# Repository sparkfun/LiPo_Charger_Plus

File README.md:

SparkFun LiPo Charger Plus
========================================

[*SparkFun LiPo Charger Plus (PRT-15217)*](https://www.sparkfun.com/products/15217)

The SparkFun LiPo Charger Plus is the souped-up power option in the SparkFun line of single-cell lithium polymer (LiPo) battery chargers. With this iteration, we've changed the input charge connector to USB-C and provided charge rate selection as well as optional thermal protection. Charge, power, and done LEDs clearly indicate the status of your charging process. This board can be used for any of the 2-pin JST connector single cell LiPo batteries we carry. 

With an input voltage between 3.75V-6V, the MCP73833 can charge up to a maximum rate of 1000mAh and provides two forms of thermal protection. An internal sensor maintains maximum charging rate until the die temperature of the IC reaches ~95°C; the charge controller will then reduce the charge rate to prevent overheating. The MCP73833 also has an optional input pin for an NTC (negative-temperature coefficient) thermistor, thus gating the battery against possible damage. 

Repository Contents
-------------------

* **/Hardware** - Eagle design files (.brd, .sch)

Documentation
--------------
* **[SparkFun Fritzing Part](https://github.com/sparkfun/Fritzing_Parts/blob/main/products/15217_sfe_LiPo_Charger_Plus.fzpz)** - Fritzing diagrams for SparkFun products.
* **[Hookup Guide](https://learn.sparkfun.com/tutorials/lipo-charger-plus-hookup-guide)** - Basic hookup guide for the SparkFun LiPo Charger Plus.

License Information
-------------------

This product is _**open source**_!

Please review the LICENSE.md file for license information.

If you have any questions or concerns on licensing, please contact technical support on our [SparkFun forums](https://forum.sparkfun.com/viewforum.php?f=152).

Distributed as-is; no warranty is given.

- Your friends at SparkFun.

_<COLLABORATION CREDIT>_

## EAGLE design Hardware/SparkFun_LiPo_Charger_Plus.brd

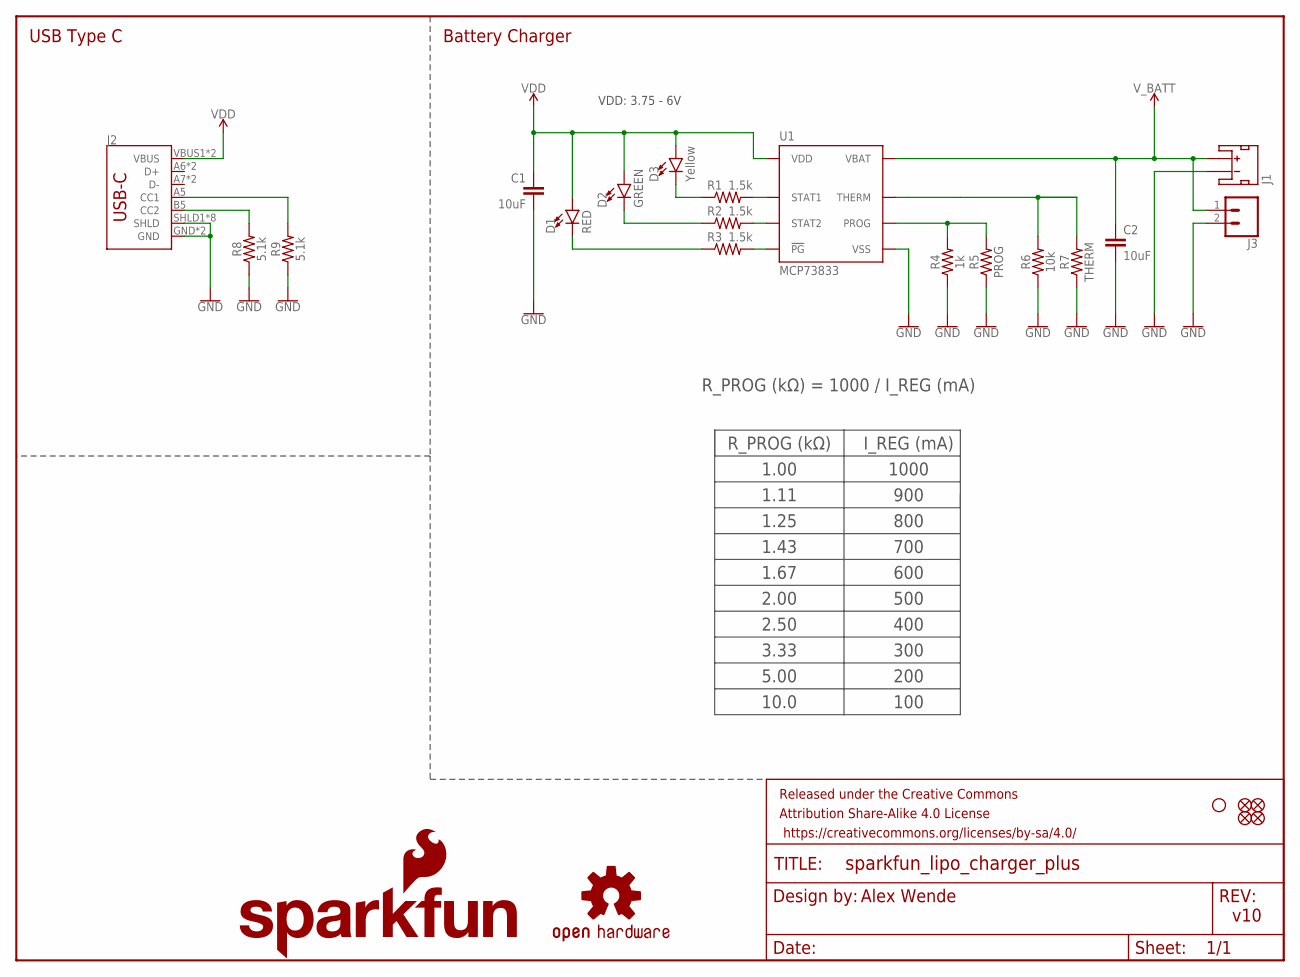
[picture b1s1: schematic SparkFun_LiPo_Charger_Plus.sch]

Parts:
C1, C2: 10uF; 0603
D1: RED; LED-0603
D2: GREEN; LED-0603
D3: Yellow; LED-0603
FD1, FD2, FD3, FD4: FIDUCIALUFIDUCIAL; FIDUCIAL-MICRO
FRAME1: FRAME-LETTER; CREATIVE_COMMONS
H1: STAND-OFF
J1: JST_2MM_MALE; JST-2-SMD
J2: USB_C16PIN; USB-C-16P
J3: CONN_021X02_NO_SILK; 1X02_NO_SILK
LOGO1: SFE_LOGO_NAME_FLAME.1_INCH; SFE_LOGO_NAME_FLAME_.1
LOGO2: OSHW-LOGOS; OSHW-LOGO-S
R1, R2, R3: 1.5k; 0603
R4: 1k; 0603
R5: PROG; AXIAL-0.3
R6: 10k; 0603
R7: THERM; AXIAL-0.3
R8, R9: 5.1k; 0603
U1: MCP73833; DFN-10

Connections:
GND: C1.2, C2.2, J1.1 (-), J2.GND, J2.GND2 (GND), J2.SHLD1 (SHLD), J2.SHLD2 (SHLD), J2.SHLD3 (SHLD), J2.SHLD4 (SHLD), J2.SHLD5 (SHLD), J2.SHLD6 (SHLD), J2.SHLD7 (SHLD), J2.SHLD8 (SHLD), J3.2, R4.1, R5.P$1 (1), R6.1, R7.P$1 (1), R8.1, R9.1, U1.P$5 (VSS), U1.P$11 (VSS)
unnamed: D1.C, R3.1
unnamed: D2.C, R2.1
unnamed: D3.C, R1.1
unnamed: J2.B5 (CC2), R8.2
unnamed: J2.A5 (CC1), R9.2
PG: R3.2, U1.P$7 (!PG)
PROG: R4.2, R5.P$2 (2), U1.P$6 (PROG)
STAT1: R1.2, U1.P$3 (STAT1)
STAT2: R2.2, U1.P$4 (STAT2)
THERM: R6.2, R7.P$2 (2), U1.P$8 (THERM)
VDD: C1.1, D1.A, D2.A, D3.A, J2.VBUS1 (VBUS), J2.VBUS2 (VBUS), U1.P$1 (VDD), U1.P$2 (VDD)
V_BATT: C2.1, J1.2 (+), J3.1, U1.P$9 (VBAT), U1.P$10 (VBAT)

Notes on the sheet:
USB Type C
Battery Charger
Alex Wende
v10
R_PROG (kΩ) = 1000 / I_REG (mA)
R_PROG (kΩ)
I_REG (mA)
1.00
1000
900
800
700
600
500
400
300
200
100
1.25
1.11
1.43
1.67
2.00
2.50
3.33
5.00
10.0
VDD: 3.75 - 6V

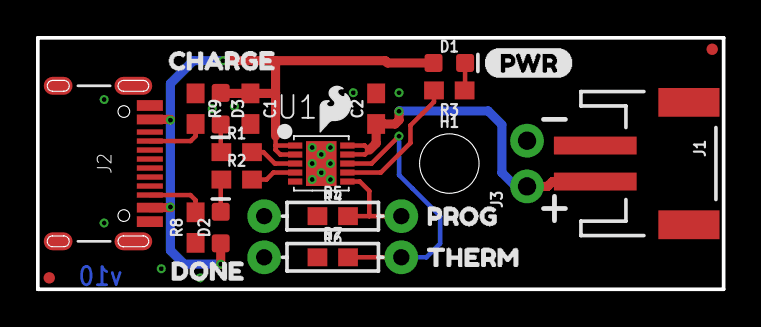
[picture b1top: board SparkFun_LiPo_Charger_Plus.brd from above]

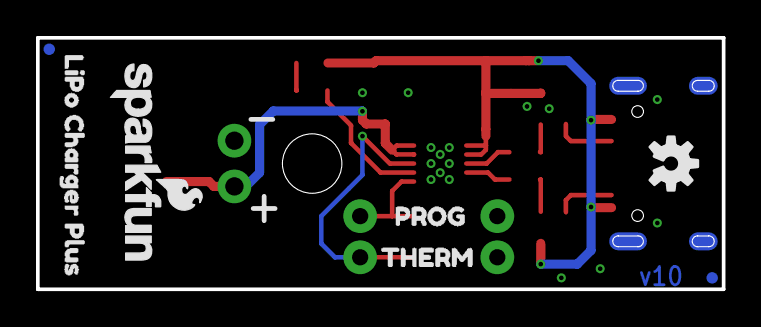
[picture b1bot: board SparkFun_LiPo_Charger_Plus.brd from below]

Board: 2 copper layers, 38.1 x 14.0 mm, 35 parts (7 on the bottom side), 13 nets.

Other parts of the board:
U$1: SFE_LOGO_FLAME_.1
U$2, U$5: PROG7
U$3: CHARGE3
U$4: DONE4
U$6, U$8: THERM8
U$7: PWR6
U$9: LIPO_CHARGER_PLUS0

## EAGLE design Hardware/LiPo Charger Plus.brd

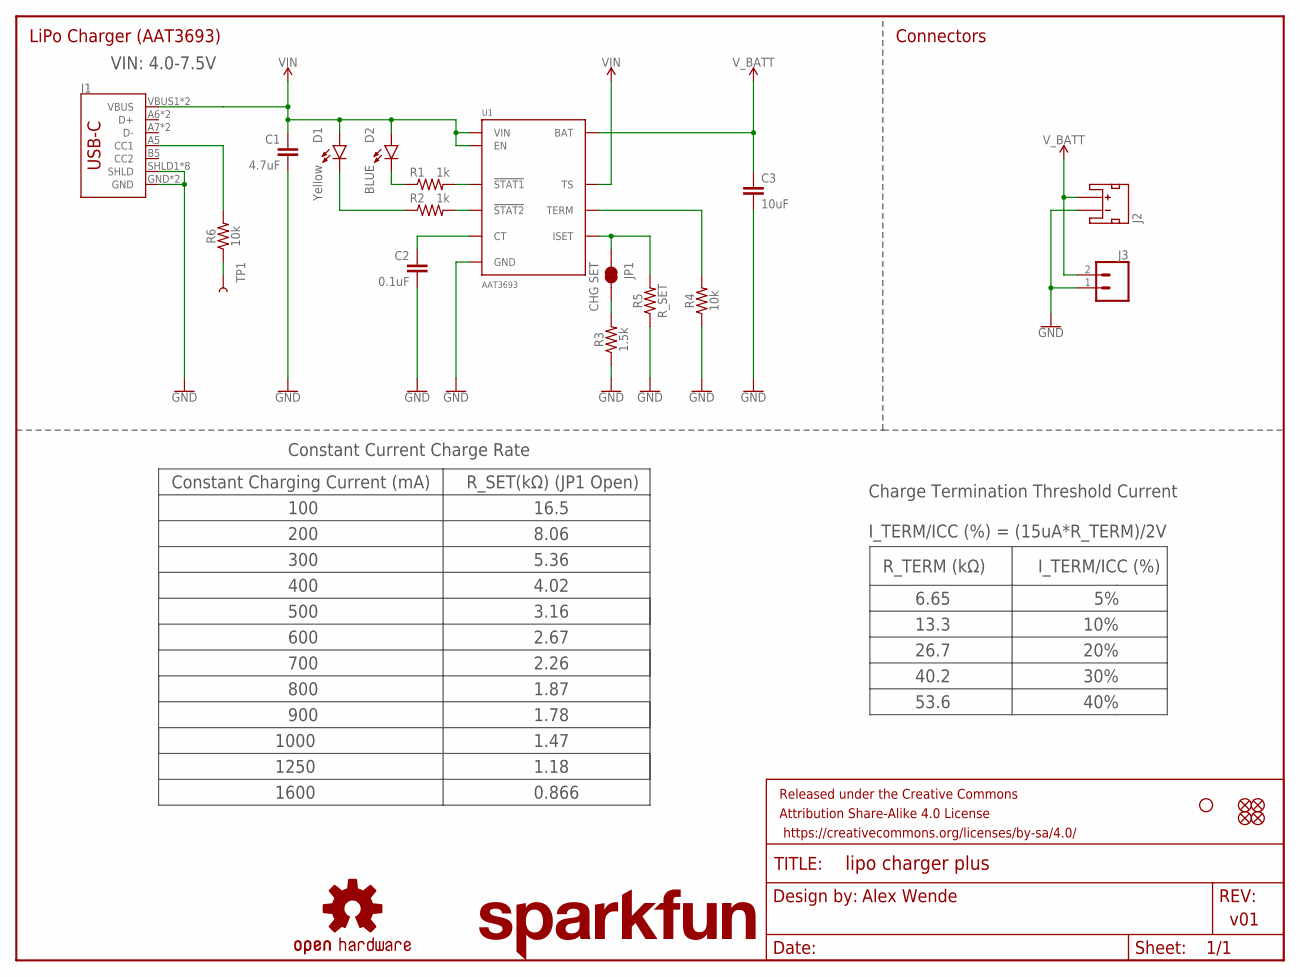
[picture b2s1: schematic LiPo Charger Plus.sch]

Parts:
C1: 4.7uF; 0603
C2: 0.1uF; 0603
C3: 10uF; 0603
D1: Yellow; LED-0603
D2: BLUE; LED-0603
FD1, FD2, FD3, FD4: FIDUCIALUFIDUCIAL; FIDUCIAL-MICRO
FRAME1: FRAME-LETTER; CREATIVE_COMMONS
H1: STAND-OFF
J1: USB_C16PIN; USB-C-16P
J2: JST_2MM_MALE; JST-2-SMD
J3: CONN_021X02_NO_SILK; 1X02_NO_SILK
JP1: CHG SET; SMT-JUMPER_2_NC_TRACE_NO-SILK
LOGO2: SFE_LOGO_NAME.1_INCH; SFE_LOGO_NAME_.1
LOGO3: OSHW-LOGOS; OSHW-LOGO-S
R1, R2: 1k; 0603
R3: 1.5k; 0603
R4, R6: 10k; 0603
R5: R_SET; AXIAL-0.3
TP1: TEST-POINTTP_15TH_THRU; TP_15TH
U1: AAT3693; WFDFN-10

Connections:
GND: C1.2, C2.2, C3.2, J1.GND, J1.GND2 (GND), J1.SHLD1 (SHLD), J1.SHLD2 (SHLD), J1.SHLD3 (SHLD), J1.SHLD4 (SHLD), J1.SHLD5 (SHLD), J1.SHLD6 (SHLD), J1.SHLD7 (SHLD), J1.SHLD8 (SHLD), J2.1 (-), J3.1, R3.1, R4.1, R5.P$1 (1), U1.P$5 (GND), U1.P$11 (GND)
unnamed: D2.C, R1.1
unnamed: JP1.2, R3.2
unnamed: J1.A5 (CC1), R6.2
unnamed: D1.C, R2.1
unnamed: R1.2, U1.P$2 (!STAT1)
unnamed: R2.2, U1.P$3 (!STAT2)
unnamed: R6.1, TP1.P$1
unnamed: C2.1, U1.P$6 (CT)
unnamed: JP1.1, R5.P$2 (2), U1.P$7 (ISET)
unnamed: R4.2, U1.P$8 (TERM)
VIN: C1.1, D1.A, D2.A, J1.VBUS1 (VBUS), J1.VBUS2 (VBUS), U1.P$1 (VIN), U1.P$4 (EN), U1.P$9 (TS)
V_BATT: C3.1, J2.2 (+), J3.2, U1.P$10 (BAT)

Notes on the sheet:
Alex Wende
v01
Charge Termination Threshold Current
I_TERM/ICC (%) = (15uA*R_TERM)/2V
R_TERM (kΩ)
I_TERM/ICC (%)
6.65
13.3
26.7
40.2
53.6
10%
20%
30%
40%
Constant Charging Current (mA)
R_SET(kΩ) (JP1 Open)
100
200
300
400
500
600
700
800
900
1000
1250
1600
16.5
8.06
5.36
4.02
3.16
2.67
2.26
1.87
1.78
1.47
1.18

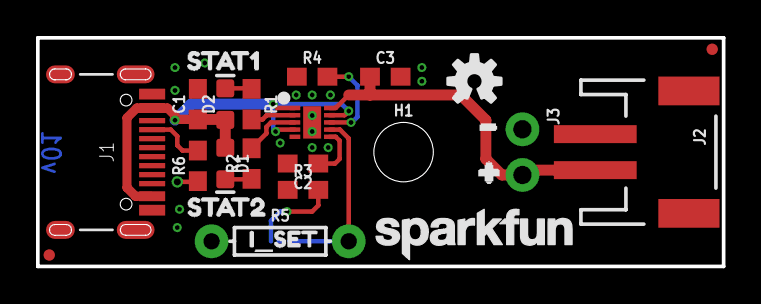
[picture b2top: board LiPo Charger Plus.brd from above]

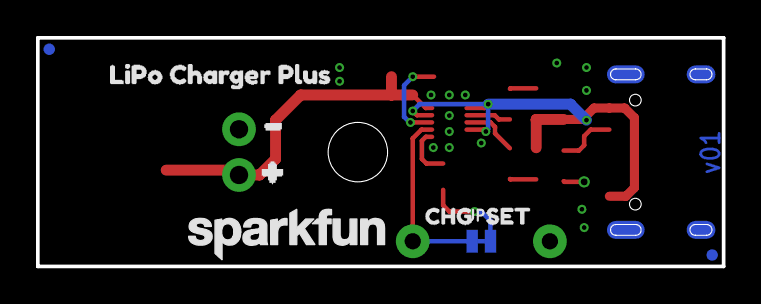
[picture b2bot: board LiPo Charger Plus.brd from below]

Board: 2 copper layers, 38.1 x 12.7 mm, 36 parts (9 on the bottom side), 13 nets.

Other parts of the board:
U$1: STAT12
U$2: STAT23
U$3: I_SET2
U$4, U$11: #1
U$5, U$12: #0
U$6: LIPO_CHARGER_PLUS5
U$7: CHG2
U$8: SET3
U$10: SFE_LOGO_NAME_.1

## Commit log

2019-02-11 QC Fixes
    -Changed engineer text from measures layer to tDocu layer
2019-04-10 v10 Update
    Added PROD_ID to U1, fixed part number ordering.
2019-04-10 QC Fixes
    Adjusted bottom silk
2019-04-11 Update SparkFun_LiPo_Charger_Plus.brd
    Moved bstop in a tiny bit
2019-05-22 Update README.md
    Updated Template
2019-05-29 Updating description

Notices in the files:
parts and their libraries:
SparkFun-Capacitors: Licensing: Creative Commons ShareAlike 4.0 International - https://creativecommons.org/licenses/by-sa/4.0
SparkFun-Aesthetics: Released under the Creative Commons Attribution Share-Alike 4.0 License
SparkFun-Aesthetics: https://creativecommons.org/licenses/by-sa/4.0
